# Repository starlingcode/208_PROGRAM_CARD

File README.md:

# Metaprogrammer
A 208 program card project

These Model 208 Program Cards are designed to interface with the “PROGRAM BOARD” edge connector of a Buchla & Associates Model 208 Stored Program Sound Source module and its reissues / compatible units. This is adapted from Dunnington Audio's KiCad project to provide standard 0.1" headers for prototyping, experimenting or re-programming.

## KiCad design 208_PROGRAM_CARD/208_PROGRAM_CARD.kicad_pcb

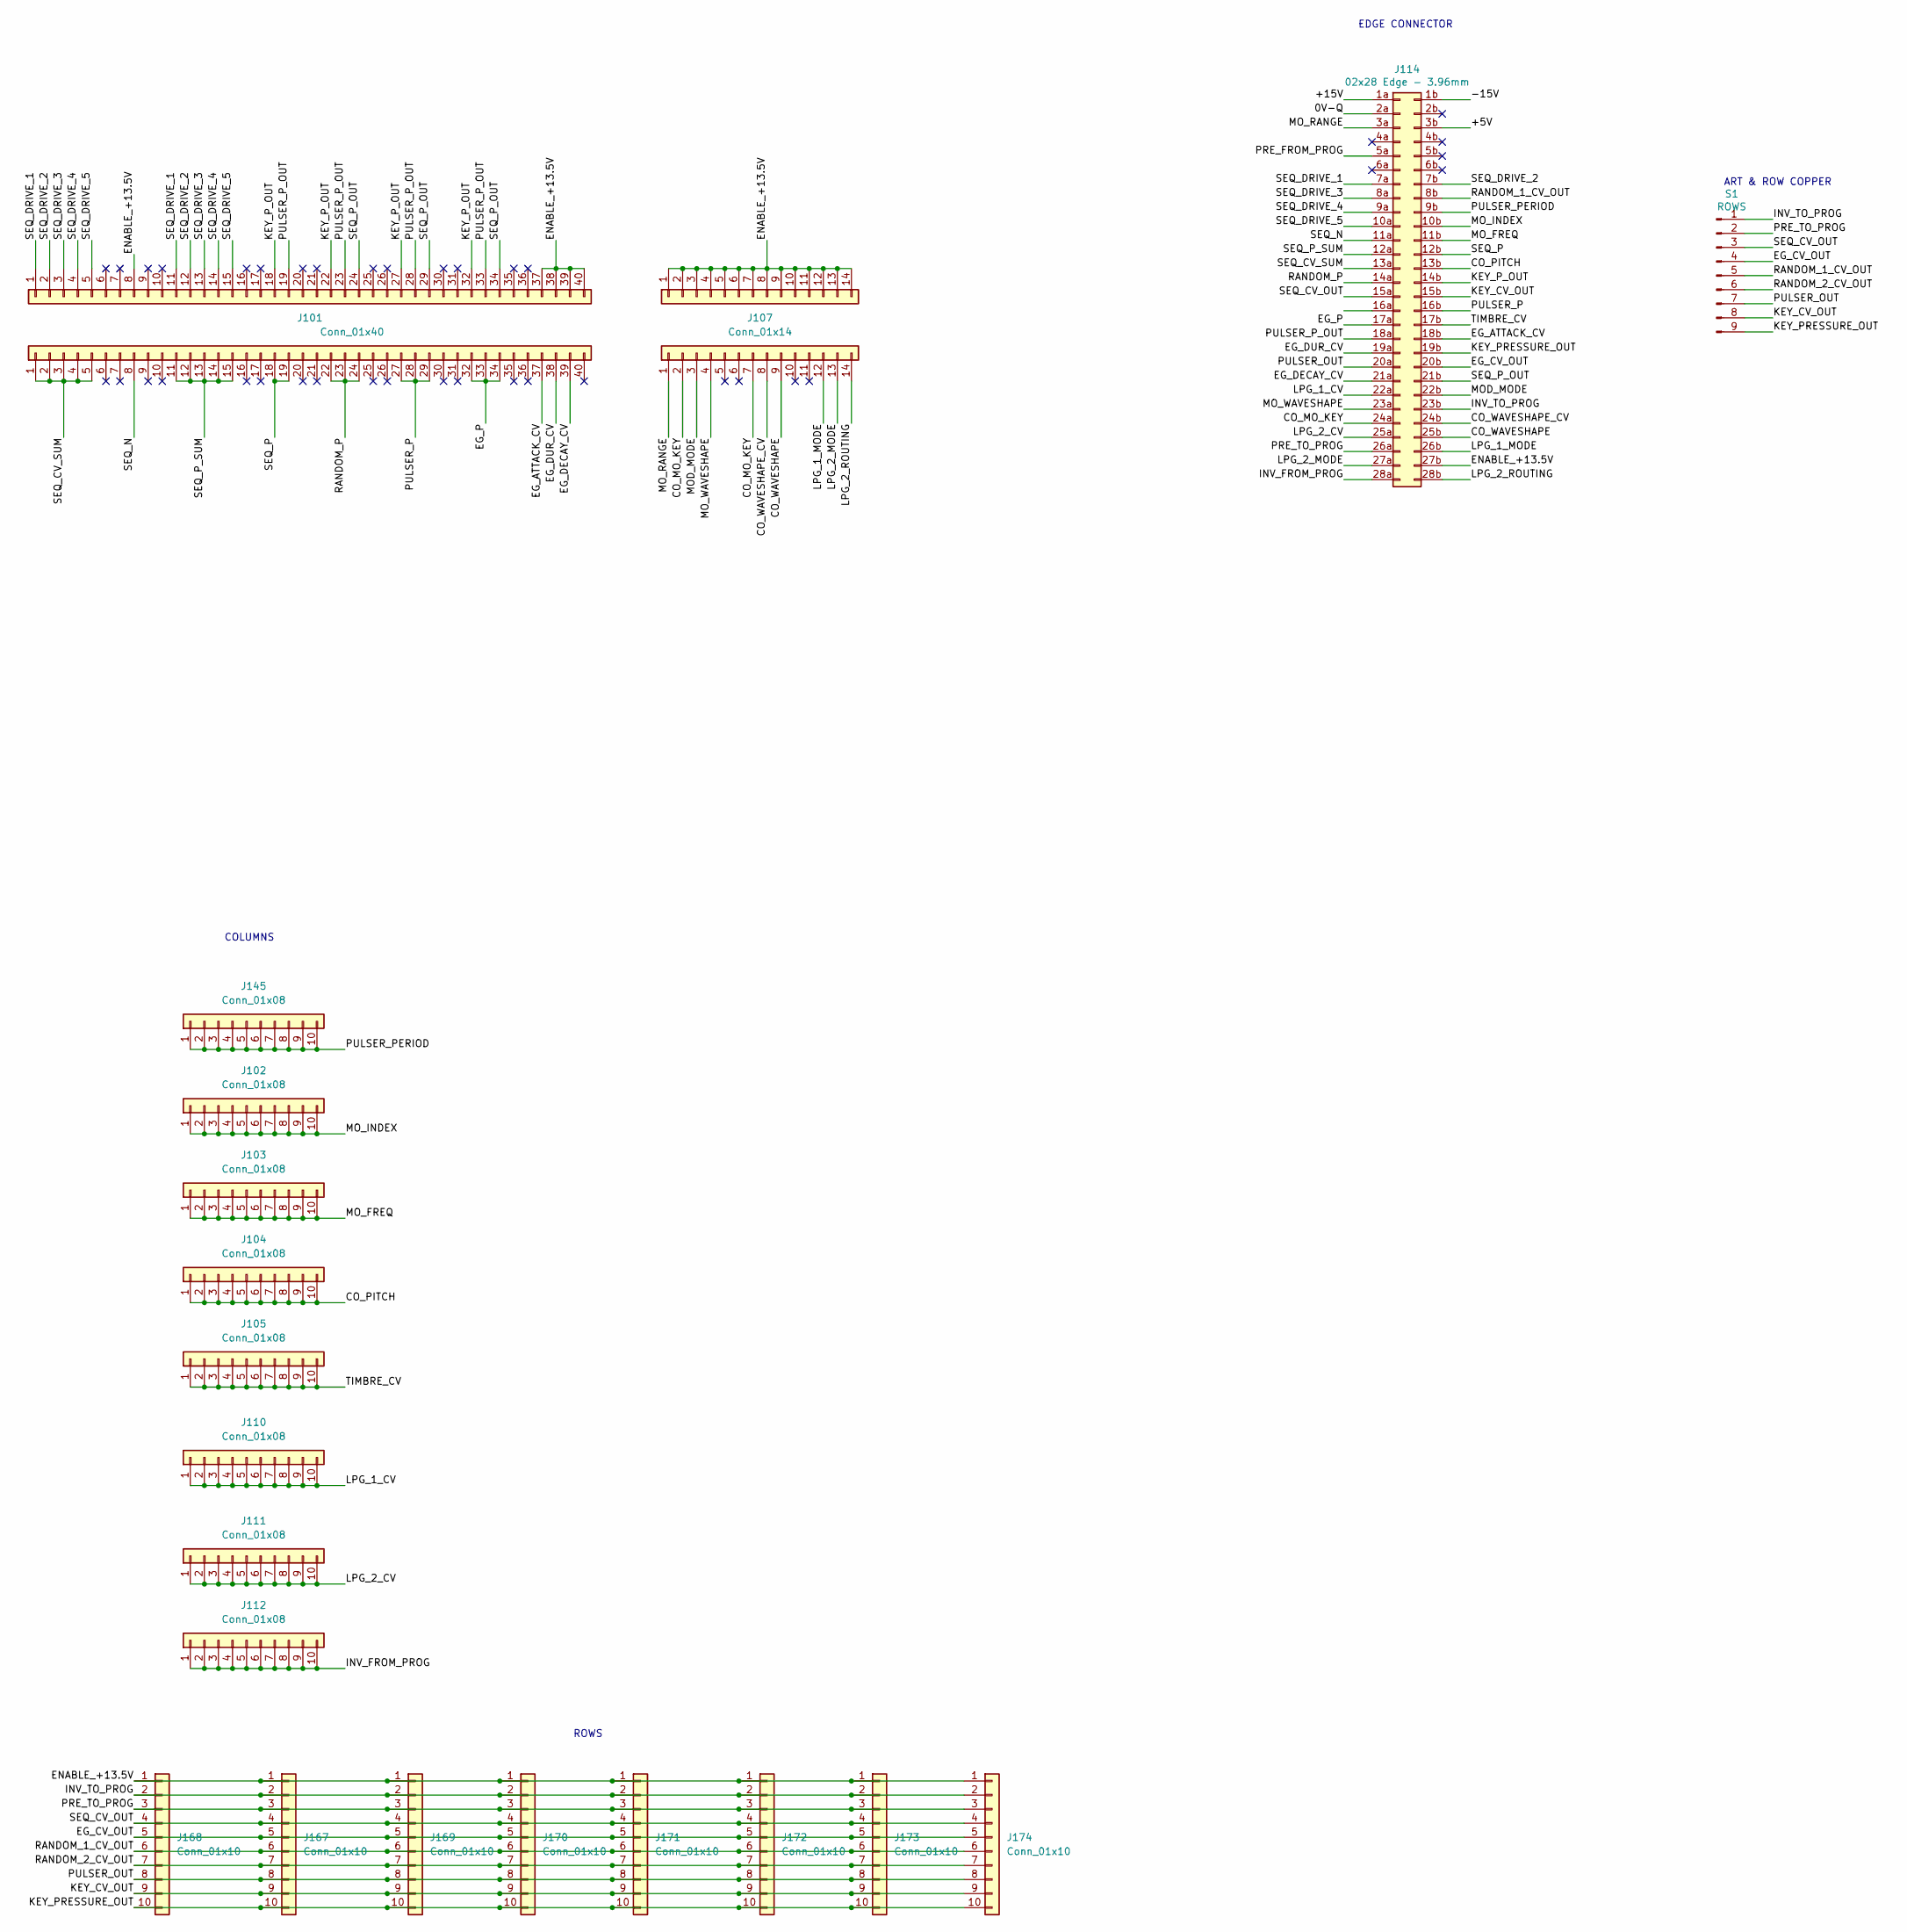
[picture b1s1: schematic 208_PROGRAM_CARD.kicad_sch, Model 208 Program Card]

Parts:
J101, J106: Conn_01x40; PinSocket_1x40_P2.54mm_Vertical
J102, J103, J104, J105, J110, J111, J112, J145: Conn_01x08; PinSocket_1x10_P2.54mm_Vertical
J107, J108: Conn_01x14; PinSocket_1x14_P2.54mm_Vertical
J114: 02x28 Edge - 3.96mm; 305-056-500-502_Mating_Edge
J167, J168, J169, J170, J171, J172, J173, J174: Conn_01x10; PinSocket_1x10_P2.54mm_Vertical
S1: ROWS; 208_PROGRAM_CARD

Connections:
/0V-Q: J114.2a
/+5V: J114.3b
/+15V: J114.1a
/-15V: J114.1b
/CO_MO_KEY: J107.2, J107.7, J114.24a
/CO_PITCH: J104.1, J104.2, J104.3, J104.4, J104.5, J104.6, J104.7, J104.8, J104.9, J104.10, J114.13b
/CO_WAVESHAPE: J107.9, J114.25b
/CO_WAVESHAPE_CV: J107.8, J114.24b
/EG_ATTACK_CV: J101.37, J114.18b
/EG_CV_OUT: J114.20b, J167.5, J168.5, J169.5, J170.5, J171.5, J172.5, J173.5, J174.5, S1.4
/EG_DECAY_CV: J101.39, J114.21a
/EG_DUR_CV: J101.38, J114.19a
/EG_P: J101.32, J101.33, J101.34, J114.17a
/ENABLE_+13.5V: J106.8, J106.37, J106.38, J106.39, J106.40, J108.1, J108.2, J108.3, J108.4, J108.5, J108.6, J108.7, J108.8, J108.9, J108.10, J108.11, J108.12, J108.13, J108.14, J114.27b, J167.1, J168.1, J169.1, J170.1, J171.1, J172.1, J173.1, J174.1
/INV_FROM_PROG: J112.1, J112.2, J112.3, J112.4, J112.5, J112.6, J112.7, J112.8, J112.9, J112.10, J114.28a
/INV_TO_PROG: J114.23b, J167.2, J168.2, J169.2, J170.2, J171.2, J172.2, J173.2, J174.2, S1.1
/KEY_CV_OUT: J114.15b, J167.9, J168.9, J169.9, J170.9, J171.9, J172.9, J173.9, J174.9, S1.8
/KEY_PRESSURE_OUT: J114.19b, J167.10, J168.10, J169.10, J170.10, J171.10, J172.10, J173.10, J174.10, S1.9
/KEY_P_OUT: J106.18, J106.22, J106.27, J106.32, J114.14b
/LPG_1_CV: J110.1, J110.2, J110.3, J110.4, J110.5, J110.6, J110.7, J110.8, J110.9, J110.10, J114.22a
/LPG_1_MODE: J107.12, J114.26b
/LPG_2_CV: J111.1, J111.2, J111.3, J111.4, J111.5, J111.6, J111.7, J111.8, J111.9, J111.10, J114.25a
/LPG_2_MODE: J107.13, J114.27a
/LPG_2_ROUTING: J107.14, J114.28b
/MOD_MODE: J107.3, J114.22b
/MO_FREQ: J103.1, J103.2, J103.3, J103.4, J103.5, J103.6, J103.7, J103.8, J103.9, J103.10, J114.11b
/MO_INDEX: J102.1, J102.2, J102.3, J102.4, J102.5, J102.6, J102.7, J102.8, J102.9, J102.10, J114.10b
/MO_RANGE: J107.1, J114.3a
/MO_WAVESHAPE: J107.4, J114.23a
/PRE_FROM_PROG: J114.5a
/PRE_TO_PROG: J114.26a, J167.3, J168.3, J169.3, J170.3, J171.3, J172.3, J173.3, J174.3, S1.2
/PULSER_OUT: J114.20a, J167.8, J168.8, J169.8, J170.8, J171.8, J172.8, J173.8, J174.8, S1.7
/PULSER_P: J101.27, J101.28, J101.29, J114.16b
/PULSER_PERIOD: J114.9b, J145.1, J145.2, J145.3, J145.4, J145.5, J145.6, J145.7, J145.8, J145.9, J145.10
/PULSER_P_OUT: J106.19, J106.23, J106.28, J106.33, J114.18a
/RANDOM_1_CV_OUT: J114.8b, J167.6, J168.6, J169.6, J170.6, J171.6, J172.6, J173.6, J174.6, S1.5
/RANDOM_2_CV_OUT: J114.16a, J167.7, J168.7, J169.7, J170.7, J171.7, J172.7, J173.7, J174.7, S1.6
/RANDOM_P: J101.22, J101.23, J101.24, J114.14a
/SEQ_CV_OUT: J114.15a, J167.4, J168.4, J169.4, J170.4, J171.4, J172.4, J173.4, J174.4, S1.3
/SEQ_CV_SUM: J101.1, J101.2, J101.3, J101.4, J101.5, J114.13a
/SEQ_DRIVE_1: J106.1, J106.11, J114.7a
/SEQ_DRIVE_2: J106.2, J106.12, J114.7b
/SEQ_DRIVE_3: J106.3, J106.13, J114.8a
/SEQ_DRIVE_4: J106.4, J106.14, J114.9a
/SEQ_DRIVE_5: J106.5, J106.15, J114.10a
/SEQ_N: J101.8, J114.11a
/SEQ_P: J101.18, J101.19, J114.12b
/SEQ_P_OUT: J106.24, J106.29, J106.34, J114.21b
/SEQ_P_SUM: J101.11, J101.12, J101.13, J101.14, J101.15, J114.12a
/TIMBRE_CV: J105.1, J105.2, J105.3, J105.4, J105.5, J105.6, J105.7, J105.8, J105.9, J105.10, J114.17b

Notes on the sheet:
COLUMNS
EDGE CONNECTOR
ROWS
ART & ROW COPPER

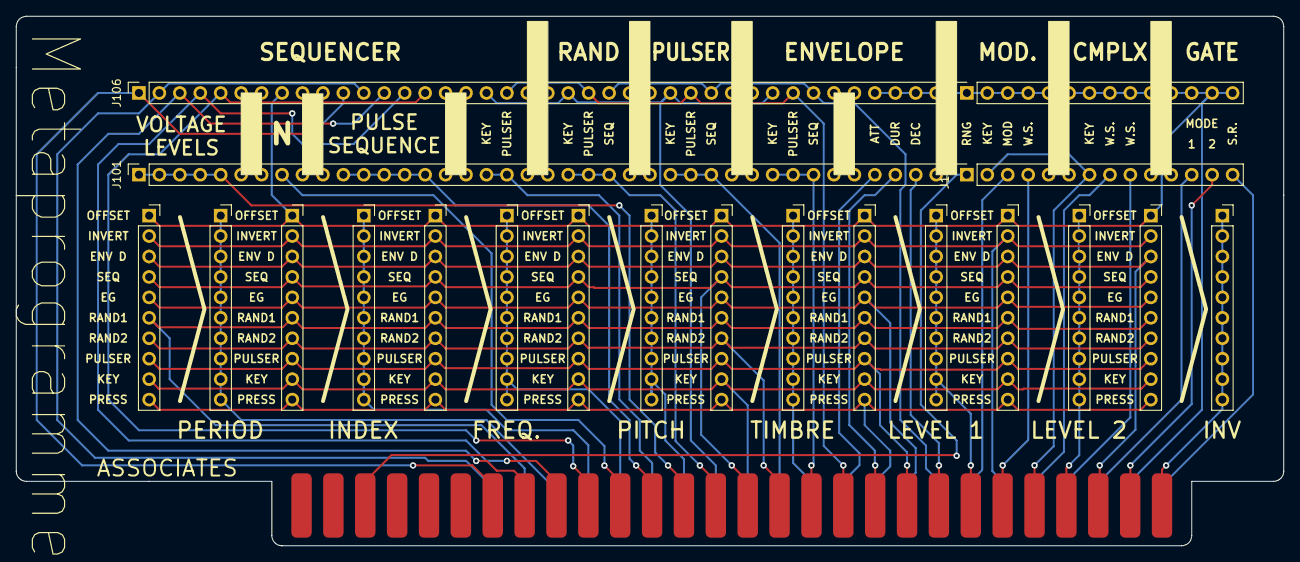
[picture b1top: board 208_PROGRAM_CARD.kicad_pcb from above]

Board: 2 copper layers, 157.5 x 65.8 mm, 21 parts (0 on the bottom side), 45 nets.

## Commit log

2024-07-16 schematic items on canvas
2024-08-01 update design
2024-08-01 clean up unnecessary files
2024-08-01 updated part info
2024-08-01 removed lock file
